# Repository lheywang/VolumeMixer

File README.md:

# 🎛️ VolumeMixer

VolumeMixer is an open-source physical volume controller that allows you to manage specific application and system volumes directly from your desktop. Featuring an OLED screen and a touch/rotary interface, it displays the icon of the application currently being controlled, offering a seamless user experience.

## ✨ Features

- Precise Control: Adjust the volume of each application independently or the global (Master) volume.
- Visual Feedback: OLED screen (SSD1306) displaying the application icon, and volume level.
- Multi-platform: Compatible with Windows and Linux.
- Plug & Play: Communication via USB (CDC Serial interface).
- Custom Hardware: PCB designed in KiCad powered by an STM32F3 microcontroller.
- Extensible: Host software written in Python, easy to modify and extend.

## 📂 Project Structure

The project is organized into three main parts:

.<br>
├── 📂 code<br>
│   ├── 📂 board       # Firmware for the STM32 microcontroller (C/C++)<br>
│   └── 📂 host        # Host software running on the PC (Python)<br>
├── 📂 data            # Graphic assets (Fonts, Bitmap icons)<br>
├── 📂 docs            # Technical documentation (Protocols, Hardware)<br>
└── 📂 pcb             # Electronic design files (KiCad)<br>

## 🛠️ Hardware

The core of the system is based on an STM32 microcontroller. Manufacturing files can be found in the pcb/ folder.

- MCU: STM32F302C8Tx
- Display: I2C OLED Screen
- Inputs: Potentiometers / Touch areas (TSC)
- Connectivity: USB Type-C.

## 🚀 Installation and Usage
### 1. Firmware (Board)

The microcontroller code is developed using STM32CubeIDE 2.0.0 / STM32CubeMX 

1. Open the project located in code/board/ with STM32CubeIDE.
2. Compile the project.
3. Flash the binary onto your STM32 board.

### 2. Host Software (PC)

The host software acts as a bridge between your operating system's audio mixer and the USB device. It uses Python and Poetry for dependency management.

Prerequisites: Python 3.x and Poetry installed.
Bash

Go to the host folder
```sh
cd code/host
```

Install dependencies
```sh
poetry install
```

Run the program
```sh
python -m poetry run .\host\main.py
```

> [!WARNING]
> Note: On Linux, ensure you have permission to access the serial port (usually by adding your user to the dialout group).
### 3. Configuration

You can configure the behavior of the host software via the .toml files located in code/host/host/config/:

 - [win.toml](https://github.com/lheywang/VolumeMixer/blob/main/code/host/host/config/win.toml) for Windows.
 - [linux.toml](https://github.com/lheywang/VolumeMixer/blob/main/code/host/host/config/linux.toml) for Linux.

## 📚 Technical Documentation

For developers who want to contribute or understand the internal workings:

  - [Communication Protocol](https://github.com/lheywang/VolumeMixer/blob/main/docs/commands.md)
  - [Screen & Buffer Management](https://github.com/lheywang/VolumeMixer/blob/main/docs/screen.m)
  - [Finite State Machine (FSM)](https://github.com/lheywang/VolumeMixer/blob/main/docs/statemachine.m)
  - [EEPROM Management](https://github.com/lheywang/VolumeMixer/blob/main/docs/eeprom.m)

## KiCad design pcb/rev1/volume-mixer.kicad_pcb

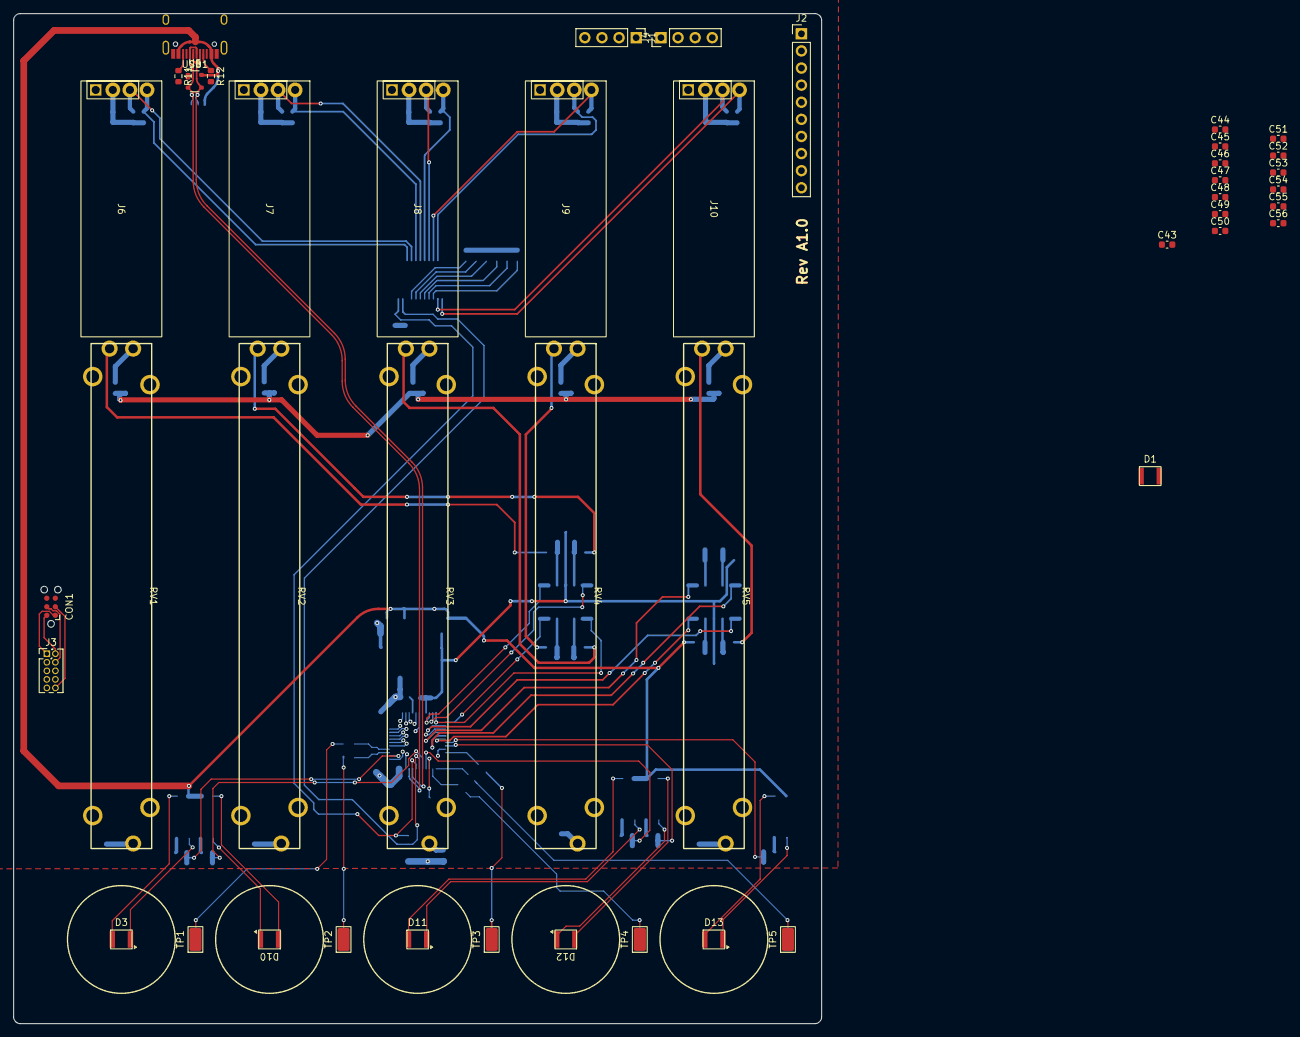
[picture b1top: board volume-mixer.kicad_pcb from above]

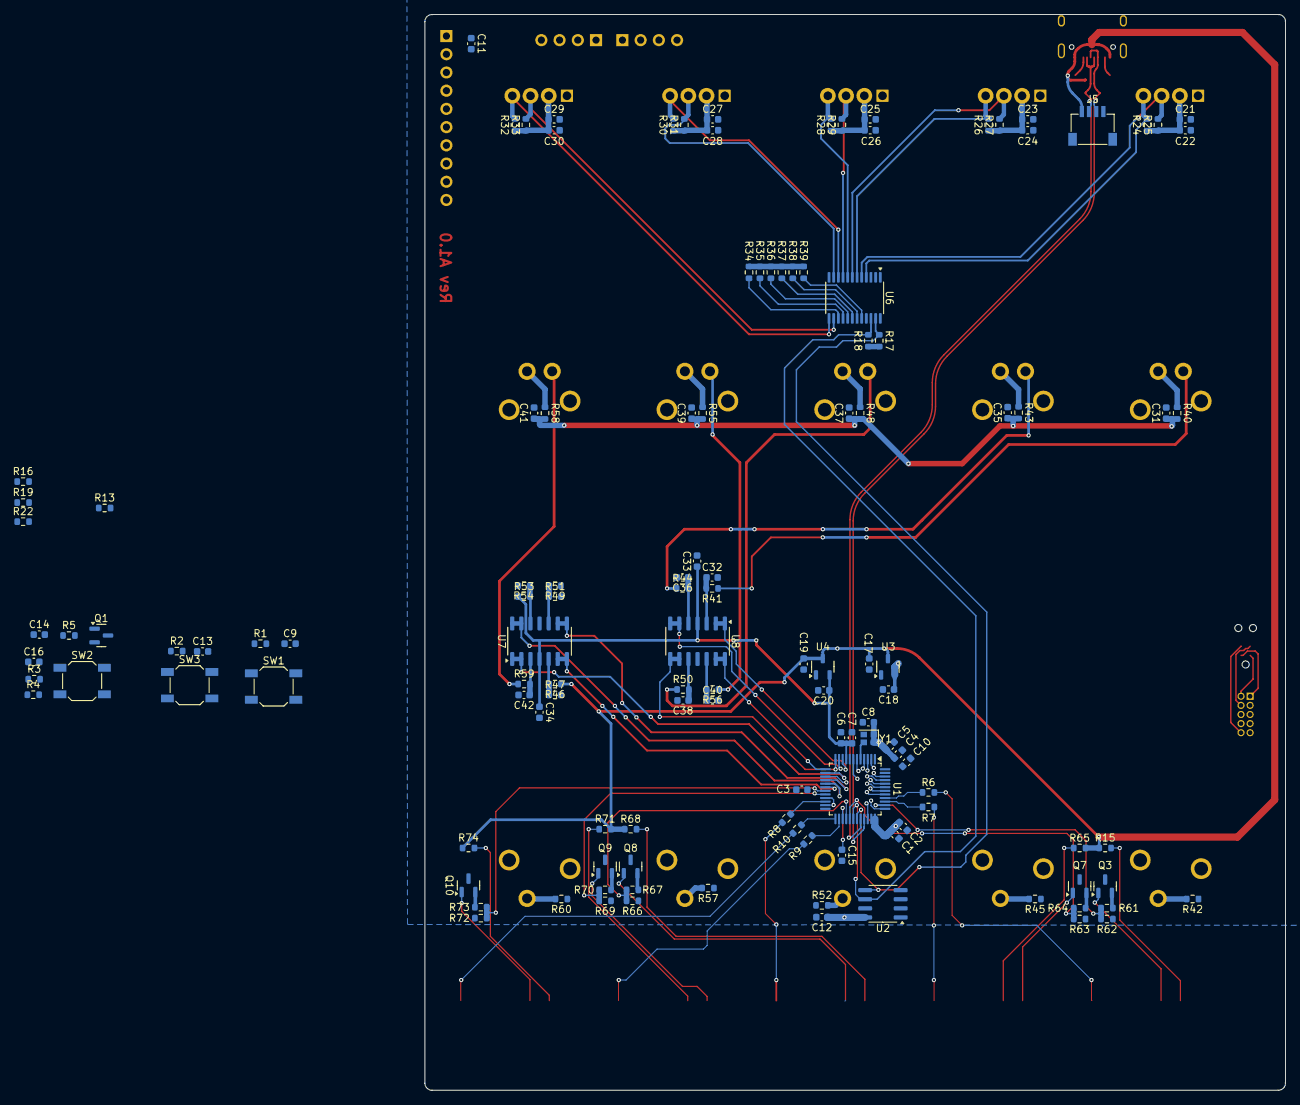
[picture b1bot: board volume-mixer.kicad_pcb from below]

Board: 4 copper layers, 120.0 x 150.0 mm, 172 parts (128 on the bottom side), 106 nets.

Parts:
C1: 4.7uF; C_0603_1608Metric
C2, C3, C4, C5, C9, C11, C12, C13, C21, C22, C23, C24, C25, C26, C27, C28, C29, C30, C31, C33, C34, C35, C37, C39, C41, C43, C44, C45, C46, C47, C48, C49, C50, C51, C52, C53, C54, C55, C56: 100nF; C_0603_1608Metric
C6: 10nF; C_0603_1608Metric
C7: 1uF; C_0603_1608Metric
C8: 47nF; C_0603_1608Metric
C10, C15: 47nF NP0; C_0603_1608Metric
C14: 4,7uF; C_0603_1608Metric
C16: 470nF; C_0603_1608Metric
C17, C18, C19, C20: 2,2uF; C_0603_1608Metric
C32, C36, C38, C40, C42: 680nF; C_0603_1608Metric
CON1: TC2030-IDC; Tag-Connect_TC2030-IDC-NL_2x03_P1.27mm_Vertical
D1, D3, D10, D11, D12, D13: LED; LED C516299
J1, J4: Conn_01x04_Pin; PinHeader_1x04_P2.54mm_Vertical
J2: Conn_01x10_Pin; PinHeader_1x10_P2.54mm_Vertical
J3: Conn_01x10_Pin; PinHeader_2x05_P1.27mm_Vertical
J5: JST; JST-SR-4
J6, J7, J8, J9, J10: Conn_01x04_Pin; Screen 0.91 I2C
Q1, Q3, Q7, Q8, Q9, Q10: NMOS; SOT-23
R1, R2, R6, R7, R8, R9, R10, R46, R47, R49, R51, R53, R54: 10k; R_0603_1608Metric
R3, R4, R62, R63, R66, R69, R72: 10K; R_0603_1608Metric
R5: 100k; R_0603_1608Metric
R11, R12: 5,1k; R_0603_1608Metric
R13, R16, R19, R22: 1k2; R_0603_1608Metric
R15, R61, R64, R65, R67, R68, R70, R71, R73, R74: 100; R_0603_1608Metric
R17, R18, R24, R25, R26, R27, R28, R29, R30, R31, R32, R33, R34, R35, R36, R37, R38, R39: 4,7K; R_0603_1608Metric
R40, R42, R43, R45, R48, R52, R55, R57, R58, R60: 2K; R_0603_1608Metric
R41, R44, R50, R56, R59: 20K; R_0603_1608Metric
RV1, RV2, RV3, RV4, RV5: PTA6043-2015CPB103; Slider Bourns PTA6043-2015CPB103
SW1, SW2, SW3: SW_Push; SW_SPST_SKQG_WithStem
TP1, TP2, TP3, TP4, TP5: TestPoint_Flag; TestPoint_Keystone_5015_Micro_Mini
U1: STM32F302C8Tx; LQFP-48_7x7mm_P0.5mm
U2: 24LC64; SOIC-8_3.9x4.9mm_P1.27mm
U3, U4: XC6206PxxxMR; SOT-23-3
U5: PRTR5V0U2X; SOT-143
U6: TCA9548APWR; TSSOP-24_4.4x7.8mm_P0.65mm
U7, U8: TL084; SOIC-14_3.9x8.7mm_P1.27mm
USB1: HRO-TYPE-C-31-M-12
Y1: 8MHz; Crystal_SMD_2016-4Pin_2.0x1.6mm

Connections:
+3V3: C1.1, C2.1, C3.1, C4.1, C5.1, C8.2, C11.1, C12.1, C18.1, C21.1, C22.1, C23.1, C24.1, C25.1, C26.1, C27.1, C28.1, C29.1, C30.1, C43.1, C44.1, C45.1, C46.1, CON1.1 (VCC), J1.3, J2.1, J3.1, J4.1, J6.2, J7.2, J8.2, J9.2, J10.2, R1.1, R2.1, R3.1, R17.1, R18.1, R24.1, R25.1, R26.1, R27.1, R28.1, R29.1, R30.1, R31.1, R32.1, R33.1, R34.1, R35.1, R36.1, R37.1, R38.1, R39.1, R49.1, SW2.2, U1.1 (VBAT), U1.24 (VDD), U1.36 (VDD), U1.48 (VDD), U2.8 (VCC), U3.2 (VO), U6.24 (VCC), Y1.1, Y1.4
/BOOT: C14.1, R4.1, SW2.1, U1.44 (BOOT0)
/CapSense0: C10.1, U1.42 (PB6)
/CapSense1: C15.1, U1.27 (PB14)
/LED CONNECTÉ: R19.2, U1.3 (PC14)
/LED FAIL: R22.2, U1.4 (PC15)
/LED ON: R16.2, U1.2 (PC13)
/OSC-OUT: U1.5 (PF0), Y1.3
/RESET: C16.1, CON1.3 (~RESET), J3.10, Q1.1 (D), R3.2, U1.7 (NRST), U6.3 (~RESET)
/SC0: J6.3, R25.2, U6.5 (SC0)
/SC1: J7.3, R27.2, U6.7 (SC1)
/SC2: J8.3, R29.2, U6.9 (SC2)
/SC3: J9.3, R31.2, U6.11 (SC3)
/SC4: J10.3, R33.2, U6.14 (SC4)
/SC5: R35.2, U6.16 (SC5)
/SC6: R37.2, U6.18 (SC6)
/SC7: R39.2, U6.20 (SC7)
/SCL: J4.2, R18.2, U1.30 (PA9), U2.6 (SCL), U6.22 (SCL)
/SD0: J6.4, R24.2, U6.4 (SD0)
/SD1: J7.4, R26.2, U6.6 (SD1)
/SD2: J8.4, R28.2, U6.8 (SD2)
/SD3: J9.4, R30.2, U6.10 (SD3)
/SD4: J10.4, R32.2, U6.13 (SD4)
/SD5: R34.2, U6.15 (SD5)
/SD6: R36.2, U6.17 (SD6)
/SD7: R38.2, U6.19 (SD7)
/SDA: J4.3, R17.2, U1.31 (PA10), U2.5 (SDA), U6.23 (SDA)
/SWCLK: CON1.4 (SWCLK), J3.4, U1.37 (PA14)
/SWDIO: CON1.2 (SWDIO), J3.2, U1.34 (PA13)
/SliderSense0: R6.1, TP1.1
/SliderSense1: R7.1, TP2.1
/SliderSense2: R8.1, TP3.1
/SliderSense3: R9.1, TP4.1
/SliderSense4: R10.1, TP5.1
D+: J5.3, U1.33 (PA12), U5.2 (IO1), USB1.6 (DP1), USB1.8 (DP2)
D-: J5.2, U1.32 (PA11), U5.3 (IO2), USB1.5 (DN2), USB1.7 (DN1)
DBG BP: C13.1, J2.7, R2.2, SW3.2, U1.6 (PF1)
DBG IO0: J2.9, U1.43 (PB7)
DBG IO1: J2.10, U1.41 (PB5)
DBG LED: J2.8, R13.2, U1.15 (PA5)
DBG RX: J2.3, U1.45 (PB8)
DBG TX: J2.5, U1.21 (PB10)
GND: C1.2, C2.2, C3.2, C4.2, C5.2, C6.2, C7.2, C8.1, C9.2, C10.2, C11.2, C12.2, C13.2, C15.2, C16.2, C17.2, C18.2, C19.2, C20.2, C21.2, C22.2, C23.2, C24.2, C25.2, C26.2, C27.2, C28.2, C29.2, C30.2, C31.2, C32.2, C33.2, C34.2, C35.2, C36.2, C37.2, C38.2, C39.2, C40.2, C41.2, C42.2, C43.2, C44.2, C45.2, C46.2, C47.2, C48.2, C49.2, C50.2, C51.2, C52.2, C53.2, C54.2, C55.2, C56.2, CON1.5 (GND), D1.1 (K), J1.4, J2.2, J2.4, J2.6, J3.3, J3.5, J3.9, J4.4, J5.4, J6.1, J7.1, J8.1, J9.1, J10.1, Q1.3 (S), Q3.3 (S), Q7.3 (S), Q8.3 (S), Q9.3 (S), Q10.3 (S), R4.2, R5.2, R11.2, R12.2, R42.1, R45.1, R47.2, R51.2, R52.1, R54.2, R57.1, R60.1, R62.1, R63.1, R66.1, R69.1, R72.1, RV1.M, RV2.M, RV3.M, RV4.M, RV5.M, SW1.1, SW3.1, U1.8 (VSSA), U1.23 (VSS), U1.35 (VSS), U1.47 (VSS), U2.1 (A0), U2.2 (A1), U2.3 (A2), U2.4 (GND), U2.7 (WP), U3.1 (GND), U4.1 (GND), U5.1 (GND), U6.1 (A0), U6.2 (A1), U6.12 (GND), U6.21 (A2), U7.11 (V-), U8.11 (V-), USB1.1 (GND), USB1.12 (GND), USB1.13 (SHIELD), Y1.2
Mute0Led: R61.1, R62.2, U1.38 (PA15)
Mute1Led: R63.2, R64.1, U1.29 (PA8)
Mute2Led: R66.2, R67.1, U1.28 (PB15)
Mute3Led: R69.2, R70.1, U1.20 (PB2)
Mute4Led: R72.2, R73.1, U1.19 (PB1)
unnamed: D1.2 (A), R13.1
unnamed: D3.2 (A), R15.2
unnamed: D3.1 (K), Q3.1 (D)
unnamed: D10.2 (A), R65.2
unnamed: D10.1 (K), Q7.1 (D)
unnamed: D11.2 (A), R68.2
unnamed: D11.1 (K), Q8.1 (D)
unnamed: D12.2 (A), R71.2
unnamed: D12.1 (K), Q9.1 (D)
unnamed: D13.2 (A), R74.2
unnamed: D13.1 (K), Q10.1 (D)
unnamed: C14.2, Q1.2 (G), R5.1
unnamed: Q3.2 (G), R61.2
unnamed: Q7.2 (G), R64.2
unnamed: Q8.2 (G), R67.2
unnamed: Q9.2 (G), R70.2
unnamed: Q10.2 (G), R73.2
unnamed: R40.1, RV1.1
unnamed: R41.1, RV1.2
unnamed: R42.2, RV1.3
unnamed: R43.1, RV2.1
unnamed: R44.1, RV2.2
unnamed: R45.2, RV2.3
unnamed: R48.1, RV3.1
unnamed: R50.1, RV3.2
unnamed: R52.2, RV3.3
unnamed: R55.1, RV4.1
unnamed: R56.1, RV4.2
unnamed: R57.2, RV4.3
unnamed: R58.1, RV5.1
unnamed: R59.1, RV5.2
unnamed: R60.2, RV5.3
unnamed: C42.1, R59.2, U7.3 (+)
unnamed: R46.2, R47.1, U7.5 (+)
unnamed: R49.2, R51.1, U7.10 (+)
unnamed: R53.2, R54.1, U7.12 (+)
unnamed: C32.1, R41.2, U8.3 (+)
unnamed: C36.1, R44.2, U8.5 (+)
unnamed: C38.1, R50.2, U8.10 (+)
unnamed: C40.1, R56.2, U8.12 (+)
unnamed: R12.1, USB1.4 (CC1)
unnamed: R11.1, USB1.10 (CC2)
PowerOnBP: C9.1, R1.2, SW1.2, U1.46 (PB9)
SLIDER_0_mute: R6.2, U1.40 (PB4)
SLIDER_1_mute: R7.2, U1.39 (PB3)
SLIDER_2_mute: R8.2, U1.22 (PB11)
SLIDER_3_mute: R9.2, U1.26 (PB13)
SLIDER_4_mute: R10.2, U1.25 (PB12)
Slider0: U1.10 (PA0), U8.1, U8.2 (-)
Slider1: U1.11 (PA1), U8.6 (-), U8.7
Slider2: U1.12 (PA2), U8.8, U8.9 (-)
Slider3: U1.13 (PA3), U8.13 (-), U8.14
Slider4: U1.14 (PA4), U7.1, U7.2 (-)
VBUS: C17.1, C19.1, C48.1, C49.1, C50.1, C51.1, C52.1, C53.1, C54.1, C55.1, C56.1, J1.1, J5.1, R15.1, R46.1, R65.1, R68.1, R71.1, R74.1, U3.3 (VI), U4.3 (VI), U5.4 (VCC), USB1.2 (VBUS), USB1.11 (VBUS)
Vana: C6.1, C7.1, C20.1, C31.1, C33.1, C34.1, C35.1, C37.1, C39.1, C41.1, C47.1, J1.2, R40.2, R43.2, R48.2, R53.1, R55.2, R58.2, U1.9 (VDDA), U4.2 (VO), U7.4 (V+), U8.4 (V+)
Vref USB: U1.18 (PB0), U7.6 (-), U7.7
Vref ana: U1.17 (PA7), U7.13 (-), U7.14
Vref digi: U1.16 (PA6), U7.8, U7.9 (-)

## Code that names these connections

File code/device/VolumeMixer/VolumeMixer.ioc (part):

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Mcu.Name=STM32F301C(6-8)Tx
Mcu.Package=LQFP48
Mcu.UserName=STM32F301C8Tx
PA0.GPIOParameters=GPIO_Label
PA0.GPIO_Label=Slider0
PA0.Mode=IN1-Single-Ended
PA0.Signal=ADC1_IN1
PA1.GPIOParameters=GPIO_Label
PA1.GPIO_Label=Slider1
PA1.Mode=IN2-Single-Ended
PA1.Signal=ADC1_IN2
PA10.GPIOParameters=GPIO_Label
PA10.GPIO_Label=SDA
PA10.Mode=I2C
PA10.Signal=I2C2_SDA
PA11.GPIOParameters=GPIO_Label
PA11.GPIO_Label=D-
PA11.Signal=GPIO_Analog
PA12.GPIOParameters=GPIO_Label
PA12.GPIO_Label=D+
PA12.Signal=GPIO_Analog
PA13.GPIOParameters=GPIO_Label
PA13.GPIO_Label=SWDIO
PA13.Mode=Serial_Wire
PA13.Signal=SYS_JTMS-SWDIO
PA14.GPIOParameters=GPIO_Label
PA14.GPIO_Label=SWCLK
PA14.Mode=Serial_Wire
PA14.Signal=SYS_JTCK-SWCLK
PA15.GPIOParameters=GPIO_Label
PA15.GPIO_Label=Mute0Led
PA15.Signal=GPIO_Output
PA2.GPIOParameters=GPIO_Label
PA2.GPIO_Label=Slider2
PA2.Mode=IN3-Single-Ended
PA2.Signal=ADC1_IN3
PA3.GPIOParameters=GPIO_Label
PA3.GPIO_Label=Slider3
PA3.Mode=IN4-Single-Ended
PA3.Signal=ADC1_IN4
PA4.GPIOParameters=GPIO_Label
PA4.GPIO_Label=Slider4
PA4.Mode=IN5-Single-Ended
PA4.Signal=ADC1_IN5
PA5.GPIOParameters=GPIO_Label
PA5.GPIO_Label=DBG_LED
PA5.Signal=GPIO_Output
PA6.GPIOParameters=GPIO_Label
PA6.GPIO_Label=Vrefdigital
PA6.Signal=ADCx_IN10
PA7.GPIOParameters=GPIO_Label,GPIO_Mode
PA7.GPIO_Label=VrefSupply
PA7.GPIO_Mode=GPIO_MODE_ANALOG
PA7.Mode=IN15-Single-Ended
PA7.Signal=ADC1_IN15
PA8.GPIOParameters=GPIO_Label
PA8.GPIO_Label=Mute1Led
PA8.Signal=GPIO_Output
PA9.GPIOParameters=GPIO_Label
PA9.GPIO_Label=SCL
PA9.Mode=I2C
PA9.Signal=I2C2_SCL
PB0.GPIOParameters=GPIO_Label
PB0.GPIO_Label=VrefPot
PB0.Mode=IN11-Single-Ended
PB0.Signal=ADC1_IN11
PB1.GPIOParameters=GPIO_Label
PB1.GPIO_Label=Mute3Led
PB1.Signal=GPIO_Output
PB10.GPIOParameters=GPIO_Label
PB10.GPIO_Label=DBG_TX
PB10.Mode=Asynchronous
PB10.Signal=USART3_TX
PB11.GPIOParameters=GPIO_Label
PB11.GPIO_Label=Slider3Mute
PB11.Mode=G6_IO1-Channel
PB11.Signal=TSC_G6_IO1
PB12.GPIOParameters=GPIO_Label
PB12.GPIO_Label=Slider4Mute
PB12.Mode=G6_IO2-Channel
PB12.Signal=TSC_G6_IO2
PB13.GPIOParameters=GPIO_Label
PB13.GPIO_Label=Slider5Mute
PB13.Mode=G6_IO3-Channel
PB13.Signal=TSC_G6_IO3
PB14.GPIOParameters=GPIO_Label
PB14.GPIO_Label=TSC_C2
PB14.Mode=G6_IO4-Sampling
PB14.Signal=TSC_G6_IO4
PB15.GPIOParameters=GPIO_Label
PB15.GPIO_Label=Mute2Led
PB15.Signal=GPIO_Output
PB2.GPIOParameters=GPIO_Label
PB2.GPIO_Label=Mute4Led
PB2.Signal=GPIO_Output
PB3.GPIOParameters=GPIO_Label
PB3.GPIO_Label=Slider1Mute
PB3.Mode=G5_IO1-Channel
PB3.Signal=TSC_G5_IO1
PB4.GPIOParameters=GPIO_Label
PB4.GPIO_Label=Slider2Mute
PB4.Mode=G5_IO2-Channel
PB4.Signal=TSC_G5_IO2
PB5.GPIOParameters=GPIO_Label
PB5.GPIO_Label=DBG_IO1
PB5.Signal=GPIO_Input
PB6.GPIOParameters=GPIO_Label
PB6.GPIO_Label=TSC_C1
PB6.Mode=G5_IO3-Sampling
PB6.Signal=TSC_G5_IO3
PB7.GPIOParameters=GPIO_Label
PB7.GPIO_Label=DBG_IO0
PB7.Signal=GPIO_Input
PB8.GPIOParameters=GPIO_Label
PB8.GPIO_Label=DBG_RX
PB8.Mode=Asynchronous
PB8.Signal=USART3_RX
PB9.GPIOParameters=GPIO_Label
PB9.GPIO_Label=PowerOnBP
PB9.Signal=GPIO_Input
PC13.GPIOParameters=GPIO_Label
PC13.GPIO_Label=PowerOnLed
PC13.Signal=GPIO_Output
PC14\ -\ OSC32_IN.GPIOParameters=GPIO_Label
PC14\ -\ OSC32_IN.GPIO_Label=DeviceErrorLed
PC14\ -\ OSC32_IN.Signal=GPIO_Output
PC15\ -\ OSC32_OUT.GPIOParameters=GPIO_Label
PC15\ -\ OSC32_OUT.GPIO_Label=DeviceConnectedLed
PC15\ -\ OSC32_OUT.Signal=GPIO_Output
PF0-OSC_IN.GPIOParameters=GPIO_Label
PF0-OSC_IN.GPIO_Label=ClkIn
PF0-OSC_IN.Mode=HSE-External-Clock-Source
PF0-OSC_IN.Signal=RCC_OSC_IN
PF1-OSC_OUT.GPIOParameters=GPIO_Label
PF1-OSC_OUT.GPIO_Label=DBG_BP
PF1-OSC_OUT.Signal=GPIO_Input
RCC.HSEPLLFreq_Value=8000000
RCC.HSE_VALUE=8000000
RCC.SYSCLKFreq_VALUE=72000000
RCC.SYSCLKSourceVirtual=RCC_SYSCLKSOURCE_PLLCLK
board=custom

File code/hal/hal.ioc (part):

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Mcu.Name=STM32F302C(6-8)Tx
Mcu.Package=LQFP48
Mcu.UserName=STM32F302C8Tx
PA0.GPIOParameters=GPIO_Label
PA0.GPIO_Label=adc_slider0
PA0.Mode=IN1-Single-Ended
PA0.Signal=ADC1_IN1
PA1.GPIOParameters=GPIO_Label
PA1.GPIO_Label=adc_slider1
PA1.Mode=IN2-Single-Ended
PA1.Signal=ADC1_IN2
PA10.GPIOParameters=GPIO_Label
PA10.GPIO_Label=sda
PA10.Mode=I2C
PA10.Signal=I2C2_SDA
PA11.GPIOParameters=GPIO_Label
PA11.GPIO_Label=dm
PA11.Mode=Device
PA11.Signal=USB_DM
PA12.GPIOParameters=GPIO_Label
PA12.GPIO_Label=dp
PA12.Mode=Device
PA12.Signal=USB_DP
PA13.GPIOParameters=GPIO_Label
PA13.GPIO_Label=swdio
PA13.Mode=Serial_Wire
PA13.Signal=SYS_JTMS-SWDIO
PA14.GPIOParameters=GPIO_Label
PA14.GPIO_Label=swclk
PA14.Mode=Serial_Wire
PA14.Signal=SYS_JTCK-SWCLK
PA15.GPIOParameters=GPIO_Label
PA15.GPIO_Label=led_mute0
PA15.Signal=GPIO_Output
PA2.GPIOParameters=GPIO_Label
PA2.GPIO_Label=adc_slider2
PA2.Mode=IN3-Single-Ended
PA2.Signal=ADC1_IN3
PA3.GPIOParameters=GPIO_Label
PA3.GPIO_Label=adc_slider3
PA3.Mode=IN4-Single-Ended
PA3.Signal=ADC1_IN4
PA4.GPIOParameters=GPIO_Label
PA4.GPIO_Label=adc_slider4
PA4.Mode=IN5-Single-Ended
PA4.Signal=ADC1_IN5
PA5.GPIOParameters=GPIO_Label
PA5.GPIO_Label=dbg_led
PA5.Signal=GPIO_Output
PA6.GPIOParameters=GPIO_Label
PA6.GPIO_Label=vref_dig
PA6.Signal=ADCx_IN10
PA7.GPIOParameters=GPIO_Label
PA7.GPIO_Label=vref_ana
PA7.Mode=IN15-Single-Ended
PA7.Signal=ADC1_IN15
PA8.GPIOParameters=GPIO_Label
PA8.GPIO_Label=led_mute1
PA8.Signal=GPIO_Output
PA9.GPIOParameters=GPIO_Label
PA9.GPIO_Label=scl
PA9.Mode=I2C
PA9.Signal=I2C2_SCL
PB0.GPIOParameters=GPIO_Label
PB0.GPIO_Label=vref_usb
PB0.Mode=IN11-Single-Ended
PB0.Signal=ADC1_IN11
PB1.GPIOParameters=GPIO_Label
PB1.GPIO_Label=led_mute3
PB1.Signal=GPIO_Output
PB10.GPIOParameters=GPIO_Label
PB10.GPIO_Label=dbg_tx
PB10.Mode=Asynchronous
PB10.Signal=USART3_TX
PB11.GPIOParameters=GPIO_Label
PB11.GPIO_Label=mute5
PB11.Mode=G6_IO1-Channel
PB11.Signal=TSC_G6_IO1
PB12.GPIOParameters=GPIO_Label
PB12.GPIO_Label=mute4
PB12.Mode=G6_IO2-Channel
PB12.Signal=TSC_G6_IO2
PB13.GPIOParameters=GPIO_Label
PB13.GPIO_Label=mute3
PB13.Mode=G6_IO3-Channel
PB13.Signal=TSC_G6_IO3
PB14.GPIOParameters=GPIO_Label
PB14.GPIO_Label=capsense1
PB14.Mode=G6_IO4-Sampling
PB14.Signal=TSC_G6_IO4
PB15.GPIOParameters=GPIO_Label
PB15.GPIO_Label=led_mute2
PB15.Signal=GPIO_Output
PB2.GPIOParameters=GPIO_Label
PB2.GPIO_Label=led_mute4
PB2.Signal=GPIO_Output
PB3.GPIOParameters=GPIO_Label
PB3.GPIO_Label=mute1
PB3.Mode=G5_IO1-Channel
PB3.Signal=TSC_G5_IO1
PB4.GPIOParameters=GPIO_Label
PB4.GPIO_Label=mute0
PB4.Mode=G5_IO2-Channel
PB4.Signal=TSC_G5_IO2
PB5.GPIOParameters=GPIO_Label
PB5.GPIO_Label=dbg_io1
PB5.Signal=GPIO_Input
PB6.GPIOParameters=GPIO_Label
PB6.GPIO_Label=capsense0
PB6.Mode=G5_IO3-Sampling
PB6.Signal=TSC_G5_IO3
PB7.GPIOParameters=GPIO_Label
PB7.GPIO_Label=dbg_io0
PB7.Signal=GPIO_Output
PB8.GPIOParameters=GPIO_Label
PB8.GPIO_Label=dbg_rx
PB8.Mode=Asynchronous
PB8.Signal=USART3_RX
PB9.GPIOParameters=GPIO_Label
PB9.GPIO_Label=bp_power
PB9.Signal=GPIO_Input
PC13.GPIOParameters=GPIO_Label
PC13.GPIO_Label=led_on
PC13.Signal=GPIO_Output
PC14\ -\ OSC32_IN.GPIOParameters=GPIO_Label
PC14\ -\ OSC32_IN.GPIO_Label=led_connect
PC14\ -\ OSC32_IN.Signal=GPIO_Output
PC15\ -\ OSC32_OUT.GPIOParameters=GPIO_Label
PC15\ -\ OSC32_OUT.GPIO_Label=led_fail
PC15\ -\ OSC32_OUT.Signal=GPIO_Output
PF0-OSC_IN.Mode=HSE-External-Clock-Source
PF0-OSC_IN.Signal=RCC_OSC_IN
PF1-OSC_OUT.GPIOParameters=GPIO_Label
PF1-OSC_OUT.GPIO_Label=dbg_bp
PF1-OSC_OUT.Signal=GPIO_Input
RCC.HSEPLLFreq_Value=8000000
RCC.HSE_VALUE=8000000
RCC.SYSCLKFreq_VALUE=72000000
RCC.SYSCLKSourceVirtual=RCC_SYSCLKSOURCE_PLLCLK
board=custom

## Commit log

2025-05-19 Create LICENSE_HW
2025-05-19 Added base repo
2025-05-19 debut du projet
2025-05-20 Added STM32 base project
2025-05-21 Added C/C++ Cube project
2025-05-22 test 1
2025-05-22 Added 3D model of the screen
2025-05-23 avancer du layout
2025-05-26 blabla
2025-05-26 Capacitive sensor layout
2025-05-26 Added base projects for all cases
2025-05-26 Added structure of a global HAL for any board : PCB or devboard
2025-05-27 BIDIBOU
2025-05-27 Restarted project
2025-05-30 Added future C code of the mixer
2025-05-30 Added some doc
2025-05-30 Updated project config
2025-05-31 Updated spec
2025-05-31 Added parser code. Not compiling for now...
2025-05-31 finished main code for the CRC unit.
2025-05-31 Added config file and corrected build issues
2025-05-31 Added hardware config to files and corrected build issues
2025-05-31 Added nucleo project for first tests
2025-06-02 imagine ça marche
2025-06-03 test
2025-06-03 je sais jamais quoi mettre en commentaires
2025-06-08 Added poetry project for host
2025-06-08 Added standard icons
2025-06-08 Added and tested first version of poetry project
2025-06-09 Renamed images
2025-06-09 Added some libs and testes pycaw
2025-06-10 Moved images
2025-06-10 Added a python project to build the images into the right format, before compilation
2025-06-10 Removed binaries files
2025-06-10 Changed a little bit the main project to remove image processing issues
2025-06-10 Updated makefile to build images
2025-06-10 Added a readme ?!?
2025-06-10 Added first abstraction base class
2025-06-10 Added an icon
2025-06-10 Added abstraction class for the device (empty for now)
2025-06-10 Added utils classes
2025-06-10 merged ?!?
2025-06-11 Added new icons
2025-06-11 Added sorting logic for apps
2025-06-11 App sorting seems to work fine, needs tests on linux now
2025-06-11 Added volume configuration function
2025-06-11 Added and tested linux code
2025-06-11 Added first elements of the device management system
2025-06-11 Updated main
2025-06-11 Added utility functions for serial management
2025-06-11 Added commands IO
2025-06-11 Added commands and corrected scale factor for the conversion between dB and %
2025-06-11 Moved and updated doc
2025-06-21 Tested some HAL elements
2025-06-21 Tried some elements with USART_RTO. Does not work...
2025-06-22 Changed architecture of the software to use a library compiled externally
2025-06-22 Added cmake for building lib
2025-06-22 Corrected cmake issues
2025-06-22 Method change
2025-06-22 Added a mixer library project
2025-06-22 Unittest are working git statusgit status
2025-06-22 Updated config to run automatically the tool
2025-06-22 Wrote unit-tests !
2025-06-23 Finished parser of the command, now it's reliable enough for our use case
2025-06-23 Added the first payload parser. Need a bit more work to finish
2025-06-24 Added DCONF parser, and it's tests
2025-06-24 Added ASYNC Command parser
2025-06-24 Added SLPOS Command builder
2025-06-24 Added an option to automatically parse the full input into defined structs
2025-06-24 Added a whole test for the whole parser
2025-06-25 Added I2C scanner for the STM32 and tested TSC
2025-06-25 Merged mixerlib into my Windows branch
2025-06-25 Changed some code
2025-06-25 Included missing files
2025-06-25 Added builder function and tests
2025-06-25 Added a utils function to show an icon in console
2025-06-26 Added a maths conversion file
2025-06-26 Updated builder test
2025-06-26 Added maths library for conversion between custom types
2025-06-26 Replaced the old strtof to a smaller equivalent (lstrtof) to save arround 21 kB of program memory !
2025-06-26 Updated project and test
2025-06-26 Sanitizized some behavior of the new conversion procedure
2025-06-26 Updated include paths and settings
2025-06-27 Added files for the handling of screen buffer building
2025-06-27 Added image data to the project
2025-06-27 Added a readme file
2025-06-27 Added an EEPROM parser and EEPROM builder to handle configuration of the device (not fully tested for now)
2025-06-27 Added a first passing test and removed minor errors
2025-06-28 Added tests for the different EEPROM routines
2025-06-29 Added new access functions for the hash table
2025-06-30 Added support for negative ADC codes for negatives offsets
2025-06-30 Added tests for the ADC conversion function
2025-06-30 Added a digital filter for the raw ADC codes, to reduce noise
2025-06-30 Added the first bases for the screen driver
2025-07-01 Changed icons data
2025-07-01 Corrected the errors on the screen buffer
2025-07-01 Added simulation of the speaker repartition
2025-07-01 Corrected last buffers issues
2025-07-01 Corrected warnings
2025-09-24 Added SSD1306 handler
2025-09-24 Updated driver
2025-09-24 Finished SSD1306 driver
2025-09-24 Added USB-Device functions and modified them
2025-09-24 Refactored main, and added the skeleton for the future FSM
2025-09-25 Updated the fsm to get closer of what we want
2025-09-25 Added some elements to connect to the VolumeMixer dvice
2025-09-25 Added the logic to accept connections over the USB CDC protocol
2025-09-25 Added EEPROM Driver (could not test it, 24CL32 is not compatible
2025-09-26 Added ADC Sampler code
2025-12-17 Corrected python code
2025-12-29 Forgot main at home, so improvised x)
2025-12-29 Updated launch code
2025-12-29 finito-pipo?
2025-12-29 Removed old Cube project
2025-12-29 Removed useless noise
2025-12-29 Added the "real" CubeIDE project for the device. Include a lot of the previously developped codes and merged all of them
2025-12-29 Removing noise
2025-12-29 Moved project to CubeIDE 2.0.0 and re-created all drivers files
2026-01-31 Added missing files
2026-01-31 Added the missing lib files
2026-02-01 Updated code
2026-02-03 Updated ignore list
2026-02-03 Re-added the lost main.py file
2026-02-03 Added logger functions into a dedicated module
2026-02-03 Added a bit more verbose when logging
2026-02-03 Formatting
2026-02-03 Added an Update function to hide logic from higher level, and formatting
2026-02-03 Added an option to enable selecting the log level, and formatting
2026-02-03 Added some logic
2026-02-03 Added an exclusion list, for apps that shall never be processed
2026-02-03 Added some securities and implemented apps exclusion
2026-02-03 Changed prints into debug logs
2026-02-03 Added status check before running commands
2026-02-03 Corrected an error where index = 1 on some command formatting
2026-02-03 Corrected invalid dict errors
2026-02-03 Removed a false log message
2026-02-03 Corrected syntax error in the ASYNC response
2026-02-03 Added the calibration procedure, need to implemented
2026-02-04 Updated main calibration procedure
2026-02-04 Added image buffer in RAM of the device
2026-02-04 Clarify serial number year format in eeprom.md
2026-02-04 Updated calibration algorithm
2026-02-04 Updated log formatting
2026-02-04 Corrected errors while parsing the DCONF command
2026-02-04 Corrected some issues
2026-02-04 Corrected errors within parsing of some commands
2026-02-05 Corrected gain formatting
2026-02-05 Improved ADC calibration procedure. Not perfect for now, need for more works
2026-02-05 Corrected errors in the C project
2026-02-05 Added temp file, IA generated to compute the calibrations values. Need to be tested
2026-02-08 Updated calibration process, now works perfectly
2026-02-08 Corrected an issue where the global offset would not be included into the header, causing errors
2026-02-08 Corrected an issue where twice the bytes number would be generated
2026-02-08 Corrected an issue with the bytes formatting
2026-02-08 Corrected errors on the host side, need to fully test it
2026-02-08 Updated ignore rules
2026-02-08 Added support of the UICON command. Works fine !
2026-02-09 Renamed categories to match the hardware ID rather than a software index
2026-02-09 Removed an offset on the icons shown
2026-02-09 Corrected buffer underflows when volume was < 0.
2026-02-09 Corrected last issues with the device
2026-02-09 Added a forced screen refresh of the screen on UICON command, guard about the SLPOS return value, and removed noisy logs
2026-02-09 Repo cleanup and documentation
2026-02-22 Merged a work folder
2026-02-22 Added case 3D files
2026-02-22 Usage modifications
